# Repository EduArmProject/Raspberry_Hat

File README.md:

# Raspberry Hat Pi 4B 

Carte **socle** du bras robotique éducatif **EduArm** : elle accueille une **Raspberry Pi 4B**, distribue l'alimentation **24 V** et le bus **CAN** vers les drivers moteurs, génère le **5 V** de la Pi et regroupe les boutons, les LED et les connecteurs d'extension. Elle se place à la base du bras.

Conçue pour le projet **EduArm** (bras robotique éducatif).

[KiCad](https://img.shields.io/badge/KiCad-10.0-314cb0) [Couches](https://img.shields.io/badge/Carte-2%20couches-blue)

| **Auteur**  | Samuel_D_    |
| ----------- | ------------ |
| **Date**    | 18/11/2026   |
| **Version** | V1           |
| **Outil**   | KiCad 10.0.0 |

---
## Sommaire

1. [Structure du dépôt](#structure-du-dépôt)
2. [Fonctionnalités](#fonctionnalités)
3. [Aperçu](#aperçu)
4. [Architecture](#architecture)
5. [Caractéristiques](#caractéristiques)
6. [Composants principaux](#composants-principaux)
7. [Protections d'entrée](#protections-dentrée)
8. [Connecteurs et interface](#connecteurs-et-interface)
9. [Brochage du Raspberry Pi](#brochage-du-raspberry-pi)

---

## Structure du dépôt

```
.
├── README.md
├── SOCLE_RASPBERRY.kicad_pro
├── SOCLE_RASPBERRY.kicad_sch
├── SOCLE_RASPBERRY.kicad_pcb
├── lib/                  # symboles, empreintes et modèles 3D
├── production/
│   ├── gerbers/
│   ├── bom.csv
│   └── positions.csv
└── docs/
    ├── SOCLE_RASPBERRY_sch.pdf
    ├── SOCLE_RASPBERRY_routage.pdf
    └── img/
```

---

## Fonctionnalités

- Support d'une **Raspberry Pi 4B** sur barrette femelle 2×20 : les ports USB et Ethernet de la Pi restent accessibles.
- **Alimentation 24 V** : une entrée et une sortie 24 V, avec un bus 24 V interne à la carte pour le bouton d'arrêt d'urgence.
- **Arrêt d'urgence (BAU)** : il coupe uniquement le `+24V_OUT` (donc les moteurs). La Pi reste alimentée pour conserver les logs et analyser les erreurs éventuelles.
- **Buck 5 V** (LM2596S-5.0) qui alimente la Pi, le bandeau LED et les connecteurs 5 V.
- **Bus CAN** vers les drivers moteurs, avec **deux options** : soit MCP2518FD + TCAN3413DR (SPI vers CAN), soit un adaptateur USB-CAN externe. Une **terminaison 120 Ω** est présente sur la carte.
- **Bus de communication** exposés : UART, I2C et SPI.
- **10 GPIO libres** (`A` à `J`) répartis sur 4 connecteurs, en 3,3 V ou 5 V.
- **Boutons** : bouton utilisateur pour allumer l'écran, bouton lumineux pour mettre le bras dans une position spéciale.
- **LED d'état** : rouge (Raspberry), jaune (Wi-Fi), verte (transmission CAN), et **bandeau WS2812B** autour de la base du bras.
- **Écran** Waveshare 7" HDMI tactile, relié directement à la Pi (HDMI + USB).

## Aperçu

### Schématique

[SOCLE_RASPBERRY_SCH.pdf](/docs/Socle_Raspberry_SCH.pdf)

### PCB

[SOCLE_RASPBERRY_PCB.pdf](/docs/Socle_Raspberry_PCB.pdf)

### Rendu 3D

---
## Architecture

```mermaid
flowchart TB
    IN["Alimentation 24 V<br/>XT30 (entrée)"] --> F1["Fusible F1"]
    F1 --> V24["+24V"]
    V24 --> BAU["Bornier BAU<br/>(arrêt d'urgence)"]
    BAU --> OUT["XT30 2+2 (sortie)<br/>+24V_OUT + CAN"]
    V24 --> BUCK["Buck LM2596S-5.0<br/>24 V vers 5 V"]
    BUCK -->|"5 V"| RPI["Raspberry Pi 4B<br/>(barrette 2x20)"]
    BUCK -->|"5 V"| STRIP["Bandeau WS2812B"]
    RPI <-->|"SPI + INT"| MCP["MCP2518FD<br/>(option 1)"]
    MCP -->|"TX / RX CAN"| TCAN["TCAN3413DR<br/>+ R4 120 ohms"]
    TCAN <--> OUT
    RPI -->|"HDMI + USB"| SCR["Écran Waveshare<br/>7 pouces"]
    RPI --- UI["Boutons et LED d'état"]
    RPI --- EXT["UART / I2C / SPI / GPIO libres"]
```

---

## Caractéristiques

| Paramètre              | Valeur                                                                      |
| ---------------------- | --------------------------------------------------------------------------- |
| Tension d'alimentation | **24 V DC** nominal (limite du LM2596 : 40 V maximum)                       |
| Sortie 5 V             | 5 V fixe, **3 A maximum** (LM2596S-5.0)                                     |
| Sortie 24 V            | Même 24 V que l'entrée, coupée par le BAU                                   |
| Pistes 24 V / GND      | 3 à 4,5 mm de large                                                         |
| Calculateur            | Raspberry Pi 4B (USB et Ethernet conservés)                                 |
| Bus CAN                | MCP2518FD (SPI) + TCAN3413DR (3,3 V), terminaison 120 Ω, ou USB-CAN externe |
| Quartz du MCP2518FD    | 40 MHz                                                                      |
| Bus exposés            | UART (1×04), I2C (1×04), SPI (1×07)                                         |
| GPIO libres            | 10 signaux (`A` à `J`) sur 4 connecteurs                                    |
| Écran                  | Waveshare 7" HDMI tactile capacitif, 1024×600                               |
| Carte                  | 2 couches                                                                   |

---

## Composants principaux

> Prix indicatifs relevés sur LCSC (novembre 2026), susceptibles de varier.

### Microcontroleur

**Raspberry Pi 4B** – enfichée sur une barrette femelle 2×20. Les ports USB et Ethernet sont ceux de la Pi. Elle est alimentée en 5 V par les broches 2 et 4 de la barrette.
### Écran

**Waveshare 7" HDMI tactile capacitif 1024×600** – [Kubii](https://www.kubii.com/fr/ecrans-supports/3789-ecran-lcd-tactile-capacitif-de-7-pouces-pour-raspberry-jetson-3272496312562.html) - 49€

| Liaison | Description |
|---|---|
| Liaison | HDMI (image) + USB (tactile et alimentation), branchés directement sur la Pi |
| Sur la carte | Seul le bouton `BTN1` (allumer l'écran) est relié à la carte |
### Alimentation 5 V

**LM2596S-5.0** (TWGMC) – régulateur buck 5 V fixe. [LCSC C5276750](https://www.lcsc.com/product-detail/C5276750.html) - 0.60€ l'unité

| Paramètre | Description |
|---|---|
| Entrée | 24 V (depuis `+24V`, avant le BAU) |
| Sortie | 5 V, 3 A maximum |
| Broche `ON/OFF` | Reliée à GND : régulateur toujours actif |
| Retour (`FEEDBACK`) | Relié à la sortie 5 V |
| Autonomie du 5 V | Reste alimenté quand le BAU est actionné 

| Réf.  | Composant                                                    | LCSC                                                            | Prix   |
| ----- | ------------------------------------------------------------ | --------------------------------------------------------------- | ------ |
| Cin1  | Condensateur 680 µF / 50 V                                   | [C48935384](https://www.lcsc.com/product-detail/C48935384.html) | –      |
| Cout1 | Condensateur 220 µF                                          | [C47344173](https://www.lcsc.com/product-detail/C47344173.html) | –      |
| L1    | Inductance FCH1050-330M, 33 µH                               | [C20415549](https://www.lcsc.com/product-detail/C20415549.html) | 1.31€  |
| D1    | Diode Schottky 1N5822 (ST), 40 V / 3 A, traversante DO-201AD | [C915962](https://www.lcsc.com/product-detail/C915962.html)     | 0.347€ |
### Transceiver CAN

Deux options sur la même carte :

|Option|Composants|
|---|---|
|1|**MCP2518FD** (SPI vers CAN-FD) + **TCAN3413DR** (transceiver 3,3 V)|
|2|Adaptateur **USB-CAN** externe (le bus CAN est le même, sur les lignes CANH / CANL)|

**TCAN3413DR** – transceiver CAN-FD 3,3 V. [LCSC C22433320](https://www.lcsc.com/product-detail/C22433320.html) - 1€ l'unité

**MCP2518FD** – contrôleur CAN-FD SPI (SOIC-14), [documentation Microchip](https://www.microchip.com/en-us/product/MCP2518FD#Documentation).

| Réf.   | Composant                         | LCSC                                                      | Prix    |
| ------ | --------------------------------- | --------------------------------------------------------- | ------- |
| Y1     | Quartz 40 MHz (YXC X322540MPB4SI) | [C9010](https://www.lcsc.com/product-detail/C9010.html)   | 0.1€    |
| C5, C6 | 22 pF (quartz)                    | –                                                         | –       |
| C7     | 100 nF (découplage MCP2518FD)     | [C24497](https://www.lcsc.com/product-detail/C24497.html) | 0.013€  |
| C3     | 100 nF (découplage TCAN3413DR)    | [C24497](https://www.lcsc.com/product-detail/C24497.html) | 0.013€  |
| R4     | 120 Ω (terminaison)               | [C17909](https://www.lcsc.com/product-detail/C17909.html) | 0.0044€ |
| C2, C4 | 22 pF (CANH / CANL vers GND)      | –                                                         | –       |
### Interface utilisateur

| Fonction                            | Connecteur            | Remarque                              |
| ----------------------------------- | --------------------- | ------------------------------------- |
| Bouton écran                        | `BTN2` (1×02)         | `BTN1` et `GND`                       |
| Bouton lumineux (position spéciale) | `Bouton_Led1` (1×05)  | Contact C / NO / NC + anneau LED 24 V |
| LED rouge                           | `LED_R1` (1×02)       | Statut de la Raspberry, via R1 330 Ω  |
| LED jaune                           | `LED_J1` (1×02)       | Statut du Wi-Fi, via R2 330 Ω         |
| LED verte                           | `LED_V1` (1×02)       | Transmission CAN, via R3 330 Ω        |
| Bandeau LED WS2812B                 | `Bandeau_Led1` (1×03) | `+5V`, donnée via R5 330 Ω, `GND`     |

Résistances 330 Ω (×4) : [LCSC C17930](https://www.lcsc.com/product-detail/C17930.html). Condensateurs 22 pF : taille CMS 0805 (×4).

---

## Protections d'entrée

L'alimentation 24 V traverse un fusible avant d'atteindre le buck et la sortie vers les moteurs.

|Composant|Référence|Rôle|
|---|---|---|
|**Fusible F1**|JK30-300. [LCSC C369106](https://www.lcsc.com/product-detail/C369106.html)|Coupe le circuit en cas de court-circuit ou de surintensité prolongée. Le calibre est à valider : un fusible traversant 15 A / 32 V est à l'étude (ex. Littelfuse 0251015.MXL, [LCSC C178934](https://www.lcsc.com/product-detail/C178934.html)).|
|**Bouton d'arrêt d'urgence**|Bornier `BAU1`|Coupe uniquement `+24V_OUT` (moteurs). Le 5 V de la Pi n'est pas coupé.|

> ***Pas de protection contre l'inversion de polarité*** : les connecteurs XT30 sont détrompés. Bien faire attention au cablage avant le premier branchement 

---

## Connecteurs et interface

### Alimentation et bus CAN

|Connecteur|Type|Rôle|
|---|---|---|
|`POWER_IN1`|XT30 (1×02)|Entrée 24 V|
|`BAU1`|Bornier (1×02)|Arrêt d'urgence|
|`POWER_OUT1`|XT30 (2+2)|Sortie 24 V + bus CAN|

`POWER_IN` :

|Broche|Signal|
|:-:|---|
|1|GND|
|2|+24V_IN|

`BAU` (contact du bouton d'arrêt d'urgence, en série sur le 24 V de sortie) :

|Broche|Signal|
|:-:|---|
|1|+24V_OUT|
|2|+24V|

`POWER_OUT` :

|Broche|Signal|
|:-:|---|
|1|CANH|
|2|CANL|
|3|GND|
|4|+24V_OUT|

### Bus de communication

|Connecteur|Broche 1|Broche 2|Broche 3|Broche 4|Broche 5|Broche 6|Broche 7|
|---|---|---|---|---|---|---|---|
|`UART1` (1×04)|+3,3V|GND|UART_TX|UART_RX||||
|`I2C1` (1×04)|+3,3V|GND|I2C_SDA|I2C_SCL||||
|`SPI1` (1×07)|+3,3V|GND|SPI_MOSI|SPI_MISO|SPI_SCLK|SPI_CE0|SPI_CE1|

### GPIO libres

|Connecteur|Broche 1|Broche 2|Broche 3|Broche 4|Broche 5|
|---|---|---|---|---|---|
|`Connector_GPIO1` (1×04)|+3,3V|GND|A|B||
|`Connector_GPIO2` (1×05)|+3,3V|GND|J|I|H|
|`Connector_GPIO3` (1×04)|+5V|GND|F|G||
|`Connector_GPIO4` (1×05)|+5V|GND|E|D|C|

### Boutons

`BTN2` (bouton utilisateur, écran) :

|Broche|Signal|
|:-:|---|
|1|BTN1|
|2|GND|

`Bouton_Led1` (bouton métallique 22 mm, 1 contact inverseur, anneau LED 24 V) :

|Catégorie|Broche|Signal|
|---|:-:|---|
|Anneau LED|1|LED+ (+24V)|
|Anneau LED|2|LED− (vers le drain d'un MOSFET piloté par `BTN_LED`)|
|Contact|3|C (GND)|
|Contact|4|NO (`BTN_NO`)|
|Contact|5|NC (`BTN_NC`)|

### LED d'état

|Connecteur|Broche 1|Broche 2|
|---|---|---|
|`LED_R1` (1×02)|GND|LED_R (via R1)|
|`LED_J1` (1×02)|GND|LED_J (via R2)|
|`LED_V1` (1×02)|GND|LED_V (via R3)|

`Bandeau_Led1` (1×03) :

|Broche|Signal|
|:-:|---|
|1|GND|
|2|BANDEAU_LED (via R5)|
|3|+5V|

---

## Brochage du Raspberry Pi

### Alimentation

|Signal|Broches J1|
|---|---|
|+3,3V|1, 17|
|+5V|2, 4|
|GND|6, 9, 14, 20, 25, 30, 34, 39|

### Écran

Aucune broche : l'écran est relié en HDMI et en USB directement sur la Pi.
### Boutons

|Signal|Broche J1|GPIO|
|---|:-:|---|
|`BTN_NO`|27|GPIO0|
|`BTN_NC`|28|GPIO1|
|`BTN_LED`|29|GPIO5|
|`BTN1`|31|GPIO6|
### LED

|Signal|Broche J1|GPIO|
|---|:-:|---|
|`LED_V`|7|GPIO4|
|`LED_R`|36|GPIO16|
|`LED_J`|40|GPIO21|
|`BANDEAU_LED`|32|GPIO12|
### Bus CAN (MCP2518FD)

| Signal     | Broche J1 | GPIO   |
| ---------- | :-------: | ------ |
| `SPI_MOSI` |    19     | GPIO10 |
| `SPI_MISO` |    21     | GPIO9  |
| `SPI_SCLK` |    23     | GPIO11 |
| `SPI_CE0`  |    24     | GPIO8  |
| `INT_MCP`  |    22     | GPIO25 |
### Bus de communication

| Signal     | Broche J1 | GPIO   |
| ---------- | :-------: | ------ |
| `I2C_SDA`  |     3     | GPIO2  |
| `I2C_SCL`  |     5     | GPIO3  |
| `UART_TX`  |     8     | GPIO14 |
| `UART_RX`  |    10     | GPIO15 |
| `SPI_MOSI` |    19     | GPIO10 |
| `SPI_MISO` |    21     | GPIO9  |
| `SPI_SCLK` |    23     | GPIO11 |
| `SPI_CE0`  |    24     | GPIO8  |
| `SPI_CE1`  |    26     | GPIO7  |
### GPIO libres

|Signal|Broche J1|GPIO|
|---|:-:|---|
|`A`|33|GPIO13|
|`B`|35|GPIO19|
|`C`|13|GPIO27|
|`D`|12|GPIO18|
|`E`|11|GPIO17|
|`F`|37|GPIO26|
|`G`|38|GPIO20|
|`H`|18|GPIO24|
|`I`|16|GPIO23|
|`J`|15|GPIO22|

---

_Samuel D – Projet EduArm – 2026_

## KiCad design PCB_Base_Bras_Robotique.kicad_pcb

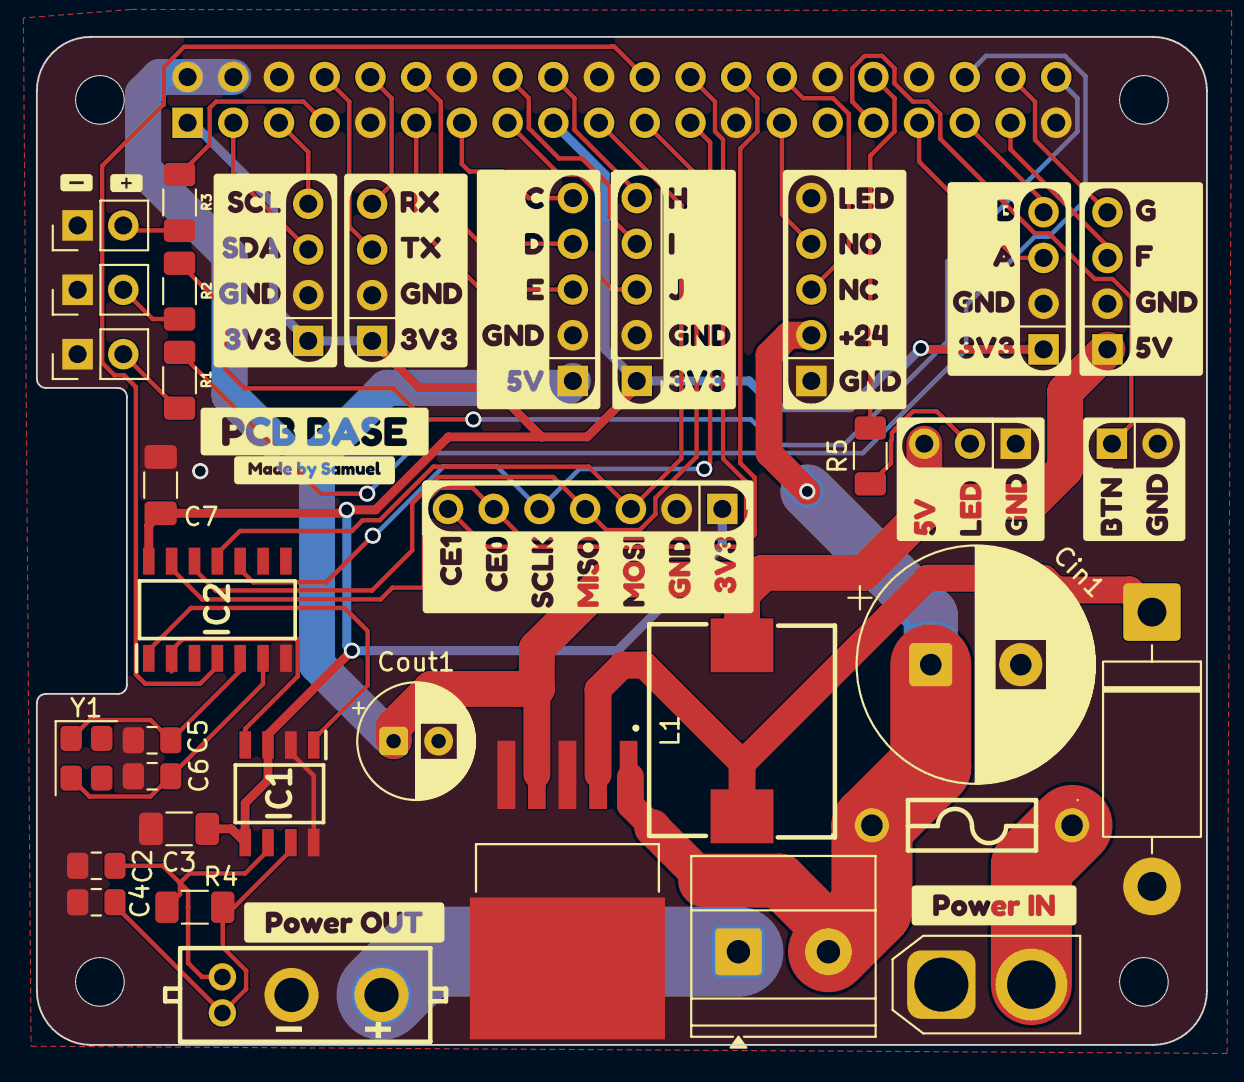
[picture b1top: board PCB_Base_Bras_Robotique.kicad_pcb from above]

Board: 2 copper layers, 65.0 x 56.0 mm, 61 parts (1 on the bottom side), 44 nets.

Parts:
BAU1: Conn_01x02; TerminalBlock_Phoenix_MKDS-1,5-2_1x02_P5.00mm_Horizontal
BTN2: Conn_01x02; PinHeader_1x02_P2.54mm_Vertical
Bandeau_Led1: Conn_01x03; PinHeader_1x03_P2.54mm_Vertical
Bouton_Led1: Conn_01x05; PinHeader_1x05_P2.54mm_Vertical
C2, C4, C5, C6: 22pF; C_0805_2012Metric_Pad1.18x1.45mm_HandSolder
C3, C7: 100nF; C_1206_3216Metric_Pad1.33x1.80mm_HandSolder
Cin1: 680uf 50v; CP_Radial_D13.0mm_P5.00mm
Connector_GPIO1, Connector_GPIO3: Conn_01x04; PinHeader_1x04_P2.54mm_Vertical
Connector_GPIO2, Connector_GPIO4: Conn_01x05; PinHeader_1x05_P2.54mm_Vertical
Cout1: 220uF; CP_Radial_D6.3mm_P2.50mm
D1: 1N5822; D_DO-201AD_P15.24mm_Horizontal
F1: 0251015.MRT1L; FUSE-TH_BD2.8-L7.1-P11.11-D0.64
I2C1: Conn_01x04; PinHeader_1x04_P2.54mm_Vertical
IC1: TCAN3413DR; SOIC127P600X175-8N
IC2: MCP2518FDT-E_SL; SOIC127P600X175-14N
J1: GPIO; PinSocket_2x20_P2.54mm_Vertical
L1: FCH1050-330M; C20415549
LED_J1: Conn_01x02; PinHeader_1x02_P2.54mm_Vertical
LED_R1: Conn_01x02; PinHeader_1x02_P2.54mm_Vertical
LED_V1: Conn_01x02; PinHeader_1x02_P2.54mm_Vertical
MH1, MH1#2, MH2, MH2#2, MH3, MH3#2, MH4, MH4#2: MountingHole_2.7mm_M2.5
POWER_IN1: Conn_01x02; AMASS_XT30U-M_1x02_P5.0mm_Vertical
POWER_OUT1: XT30; CONN-TH_XT30PB-M
R1, R2, R3, R5: 330; R_1206_3216Metric_Pad1.30x1.75mm_HandSolder
R4: 120; R_1206_3216Metric_Pad1.30x1.75mm_HandSolder
SPI1: Conn_01x07; PinHeader_1x07_P2.54mm_Vertical
UART1: Conn_01x04; PinHeader_1x04_P2.54mm_Vertical
VR1: LM2596S-5.0; TO170P1524X483-6N
Y1: 40 MHz; Crystal_SMD_3225-4Pin_3.2x2.5mm
kobee-studio-6AF39A4C: Kobee Studio; kobee-studio-6AF39A41
kobee-studio-6AF46A8A: Kobee Studio; kobee-studio-6AF46A8A
kobee-studio-6AF46E11: Kobee Studio; kobee-studio-6AF3942E
kobee-studio-6AF47BC9: Kobee Studio; kobee-studio-6AF47B7D
kobee-studio-6AF47BEA: Kobee Studio; kobee-studio-6AF47B94
kobee-studio-6AF47DA9: Kobee Studio; kobee-studio-6AF47D94
kobee-studio-6AF48B4F: Kobee Studio; kobee-studio-6AF39692
kobee-studio-6AF48B35: Kobee Studio; kobee-studio-6AF394EE
kobee-studio-6AF48B44: Kobee Studio; kobee-studio-6AF391BB
kobee-studio-6AF48C1A: Kobee Studio; kobee-studio-6AF475C9
kobee-studio-6AF48C04: Kobee Studio; kobee-studio-6AF39135
kobee-studio-6AF394B5: Kobee Studio; kobee-studio-6AF39169
kobee-studio-6AF469A6: Kobee Studio; kobee-studio-6AF46958
kobee-studio-6AF475AF: Kobee Studio; kobee-studio-6AF475AF
kobee-studio-6AF3948F: Kobee Studio; kobee-studio-6AF3919E
kobee-studio-6AF4771F: Kobee Studio; kobee-studio-6AF47703

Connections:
+3.3V: C3.1, C7.1, Connector_GPIO1.1, Connector_GPIO2.1, I2C1.1, IC1.3 (VCC), IC1.5 (SHDNV_IO), IC2.14 (VDD), J1.1, J1.17, SPI1.1, UART1.1
+5V: Bandeau_Led1.3, Connector_GPIO3.1, Connector_GPIO4.1, Cout1.1, J1.2, J1.4, L1.2, VR1.4 (FEEDBACK)
+24V: BAU1.2, Bouton_Led1.2, Cin1.1, F1.2, VR1.1 (VIN)
+24V_IN: F1.1, POWER_IN1.2
+24V_OUT: BAU1.1, POWER_OUT1.4
A: Connector_GPIO1.3, J1.33
B: Connector_GPIO1.4, J1.35
BANDEAU_LED: J1.32, R5.2
BTN1: BTN2.1, J1.31
BTN_NC: Bouton_Led1.3, J1.28
BTN_NO: Bouton_Led1.4, J1.27
C: Connector_GPIO4.5, J1.13
CANH: C4.1, IC1.7 (CANH), POWER_OUT1.1, R4.2
CANL: C2.1, IC1.6 (CANL), POWER_OUT1.2, R4.1
D: Connector_GPIO4.4, J1.12
E: Connector_GPIO4.3, J1.11
F: Connector_GPIO3.3, J1.37
G: Connector_GPIO3.4, J1.38
GND: BTN2.2, Bandeau_Led1.1, Bouton_Led1.1, Bouton_Led1.5, C2.2, C3.2, C4.2, C5.2, C6.2, C7.2, Cin1.2, Connector_GPIO1.2, Connector_GPIO2.2, Connector_GPIO3.2, Connector_GPIO4.2, Cout1.2, D1.2 (A), I2C1.2, IC1.2 (GND), IC1.8 (STB), IC2.7 (VSS), J1.6, J1.9, J1.14, J1.20, J1.25, J1.30, J1.34, J1.39, LED_J1.1, LED_R1.1, LED_V1.1, POWER_IN1.1, POWER_OUT1.3, SPI1.2, UART1.2, VR1.3 (GROUND), VR1.5 (~ON/OFF), VR1.6 (GND_TAB)
H: Connector_GPIO2.5, J1.18
I: Connector_GPIO2.4, J1.16
I2C_SCL: I2C1.4, J1.5
I2C_SDA: I2C1.3, J1.3
INT_MCP: IC2.4 (~INT), J1.22
J: Connector_GPIO2.3, J1.15
LED_J: J1.40, R2.2
LED_R: J1.36, R1.2
LED_V: J1.7, R3.2
unnamed: Bandeau_Led1.2, R5.1
unnamed: D1.1 (K), L1.1, VR1.2 (OUTPUT)
unnamed: C6.1, IC2.6 (OSC1), Y1.2
unnamed: C5.1, IC2.5 (OSC2), Y1.1
unnamed: LED_J1.2, R2.1
unnamed: LED_R1.2, R1.1
unnamed: LED_V1.2, R3.1
RX_CAN: IC1.4 (RXD), IC2.2 (RXCAN)
SPI_CE0: IC2.13 (NCS), J1.24, SPI1.6
SPI_CE1: J1.26, SPI1.7
SPI_MISO: IC2.12 (SDO), J1.21, SPI1.4
SPI_MOSI: IC2.11 (SDI), J1.19, SPI1.3
SPI_SCLK: IC2.10 (SCK), J1.23, SPI1.5
TX_CAN: IC1.1 (TXD), IC2.1 (TXCAN)
UART_RX: J1.10, UART1.4
UART_TX: J1.8, UART1.3
